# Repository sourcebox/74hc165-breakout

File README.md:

# About

KiCad project files of a breakout board containing 8 cascaded 74HC165
shift registers offering parallel-in/serial-out functionality.

This board is intended as microcontroller GPIO extension for prototyping purposes.

# License

CC-BY-4.0

By: Oliver Rockstedt <info@sourcebox.de>

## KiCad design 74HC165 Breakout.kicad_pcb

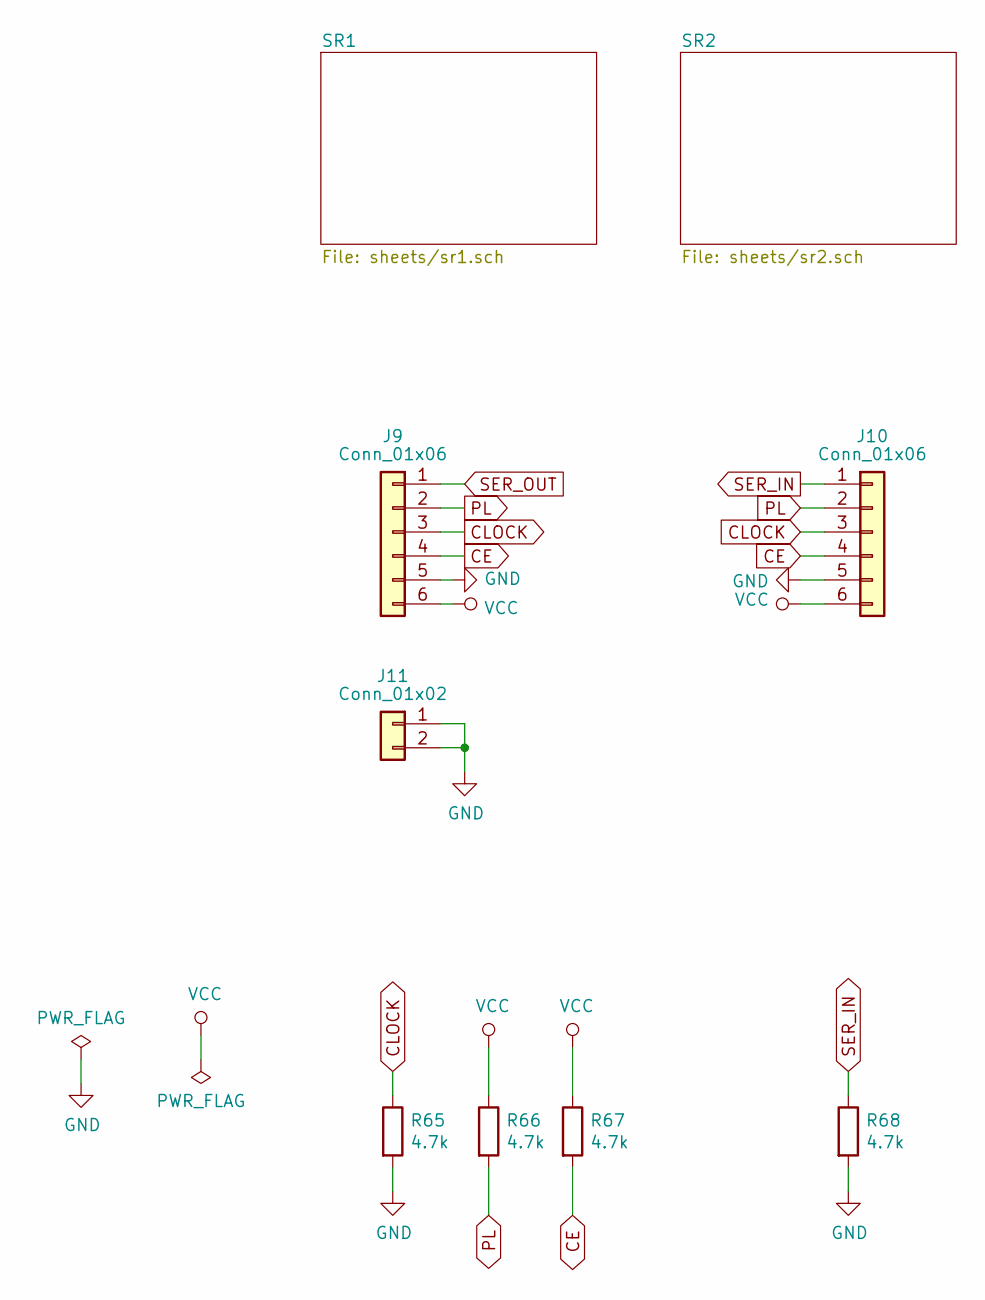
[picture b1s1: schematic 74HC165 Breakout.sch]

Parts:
J9, J10: Conn_01x06; PinHeader_1x06_P2.54mm_Vertical
J11: Conn_01x02; PinHeader_1x02_P2.54mm_Vertical
R65, R66, R67, R68: 4.7k; R_0805_2012Metric

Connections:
CE: J9.4, J10.4, R67.2; also elsewhere on the board
CLOCK: J9.3, J10.3, R65.1; also elsewhere on the board
GND: J9.5, J10.5, J11.1, J11.2, R65.2, R68.2; also elsewhere on the board
PL: J9.2, J10.2, R66.2; also elsewhere on the board
SER_IN: J10.1, R68.1; also elsewhere on the board
SER_OUT: J9.1; also elsewhere on the board
VCC: J9.6, J10.6, R66.1, R67.1; also elsewhere on the board

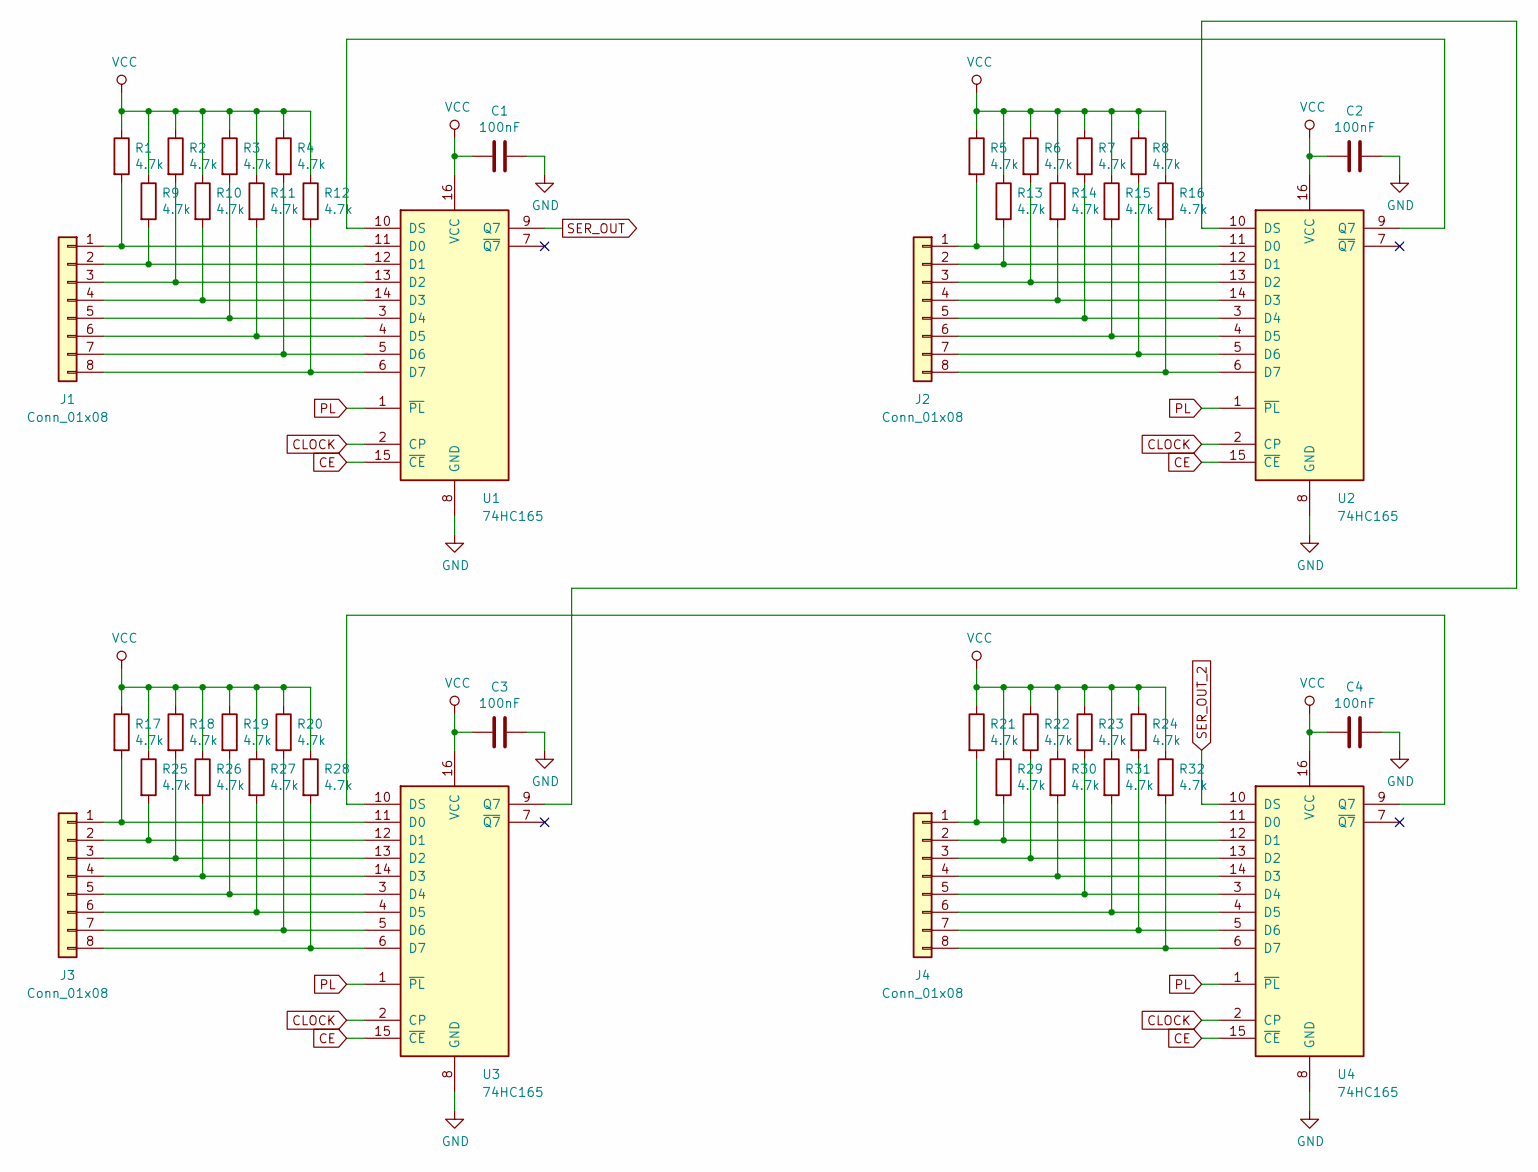
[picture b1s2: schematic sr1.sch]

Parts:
C1, C2, C3, C4: 100nF; C_0805_2012Metric
J1, J2, J3, J4: Conn_01x08; PinHeader_1x08_P2.54mm_Vertical
R1, R2, R3, R4, R5, R6, R7, R8, R9, R10, R11, R12, R13, R14, R15, R16, R17, R18, R19, R20, R21, R22, R23, R24, R25, R26, R27, R28, R29, R30, R31, R32: 4.7k; R_0805_2012Metric
U1, U2, U3, U4: 74HC165; SOIC-16_3.9x9.9mm_P1.27mm

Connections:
CE: U1.15 (~CE), U2.15 (~CE), U3.15 (~CE), U4.15 (~CE); also elsewhere on the board
CLOCK: U1.2 (CP), U2.2 (CP), U3.2 (CP), U4.2 (CP); also elsewhere on the board
GND: C1.1, C2.1, C3.1, C4.1, U1.8 (GND), U2.8 (GND), U3.8 (GND), U4.8 (GND); also elsewhere on the board
unnamed: J1.1, R1.2, U1.11 (D0)
unnamed: J1.2, R9.2, U1.12 (D1)
unnamed: J1.3, R2.2, U1.13 (D2)
unnamed: J1.4, R10.2, U1.14 (D3)
unnamed: J1.5, R3.2, U1.3 (D4)
unnamed: J1.6, R11.2, U1.4 (D5)
unnamed: J1.7, R4.2, U1.5 (D6)
unnamed: J1.8, R12.2, U1.6 (D7)
unnamed: J2.1, R5.2, U2.11 (D0)
unnamed: J2.2, R13.2, U2.12 (D1)
unnamed: J2.3, R6.2, U2.13 (D2)
unnamed: J2.4, R14.2, U2.14 (D3)
unnamed: J2.5, R7.2, U2.3 (D4)
unnamed: J2.6, R15.2, U2.4 (D5)
unnamed: J2.7, R8.2, U2.5 (D6)
unnamed: J2.8, R16.2, U2.6 (D7)
unnamed: J3.1, R17.2, U3.11 (D0)
unnamed: J3.2, R25.2, U3.12 (D1)
unnamed: J3.3, R18.2, U3.13 (D2)
unnamed: J3.4, R26.2, U3.14 (D3)
unnamed: J3.5, R19.2, U3.3 (D4)
unnamed: J3.6, R27.2, U3.4 (D5)
unnamed: J3.7, R20.2, U3.5 (D6)
unnamed: J3.8, R28.2, U3.6 (D7)
unnamed: J4.1, R21.2, U4.11 (D0)
unnamed: J4.2, R29.2, U4.12 (D1)
unnamed: J4.3, R22.2, U4.13 (D2)
unnamed: J4.4, R30.2, U4.14 (D3)
unnamed: J4.5, R23.2, U4.3 (D4)
unnamed: J4.6, R31.2, U4.4 (D5)
unnamed: J4.7, R24.2, U4.5 (D6)
unnamed: J4.8, R32.2, U4.6 (D7)
unnamed: U1.10 (DS), U2.9 (Q7)
unnamed: U2.10 (DS), U3.9 (Q7)
unnamed: U3.10 (DS), U4.9 (Q7)
PL: U1.1 (~PL), U2.1 (~PL), U3.1 (~PL), U4.1 (~PL); also elsewhere on the board
SER_OUT: U1.9 (Q7); also elsewhere on the board
SER_OUT_2: U4.10 (DS); also elsewhere on the board
VCC: C1.2, C2.2, C3.2, C4.2, R1.1, R2.1, R3.1, R4.1, R5.1, R6.1, R7.1, R8.1, R9.1, R10.1, R11.1, R12.1, R13.1, R14.1, R15.1, R16.1, R17.1, R18.1, R19.1, R20.1, R21.1, R22.1, R23.1, R24.1, R25.1, R26.1, R27.1, R28.1, R29.1, R30.1, R31.1, R32.1, U1.16 (VCC), U2.16 (VCC), U3.16 (VCC), U4.16 (VCC); also elsewhere on the board

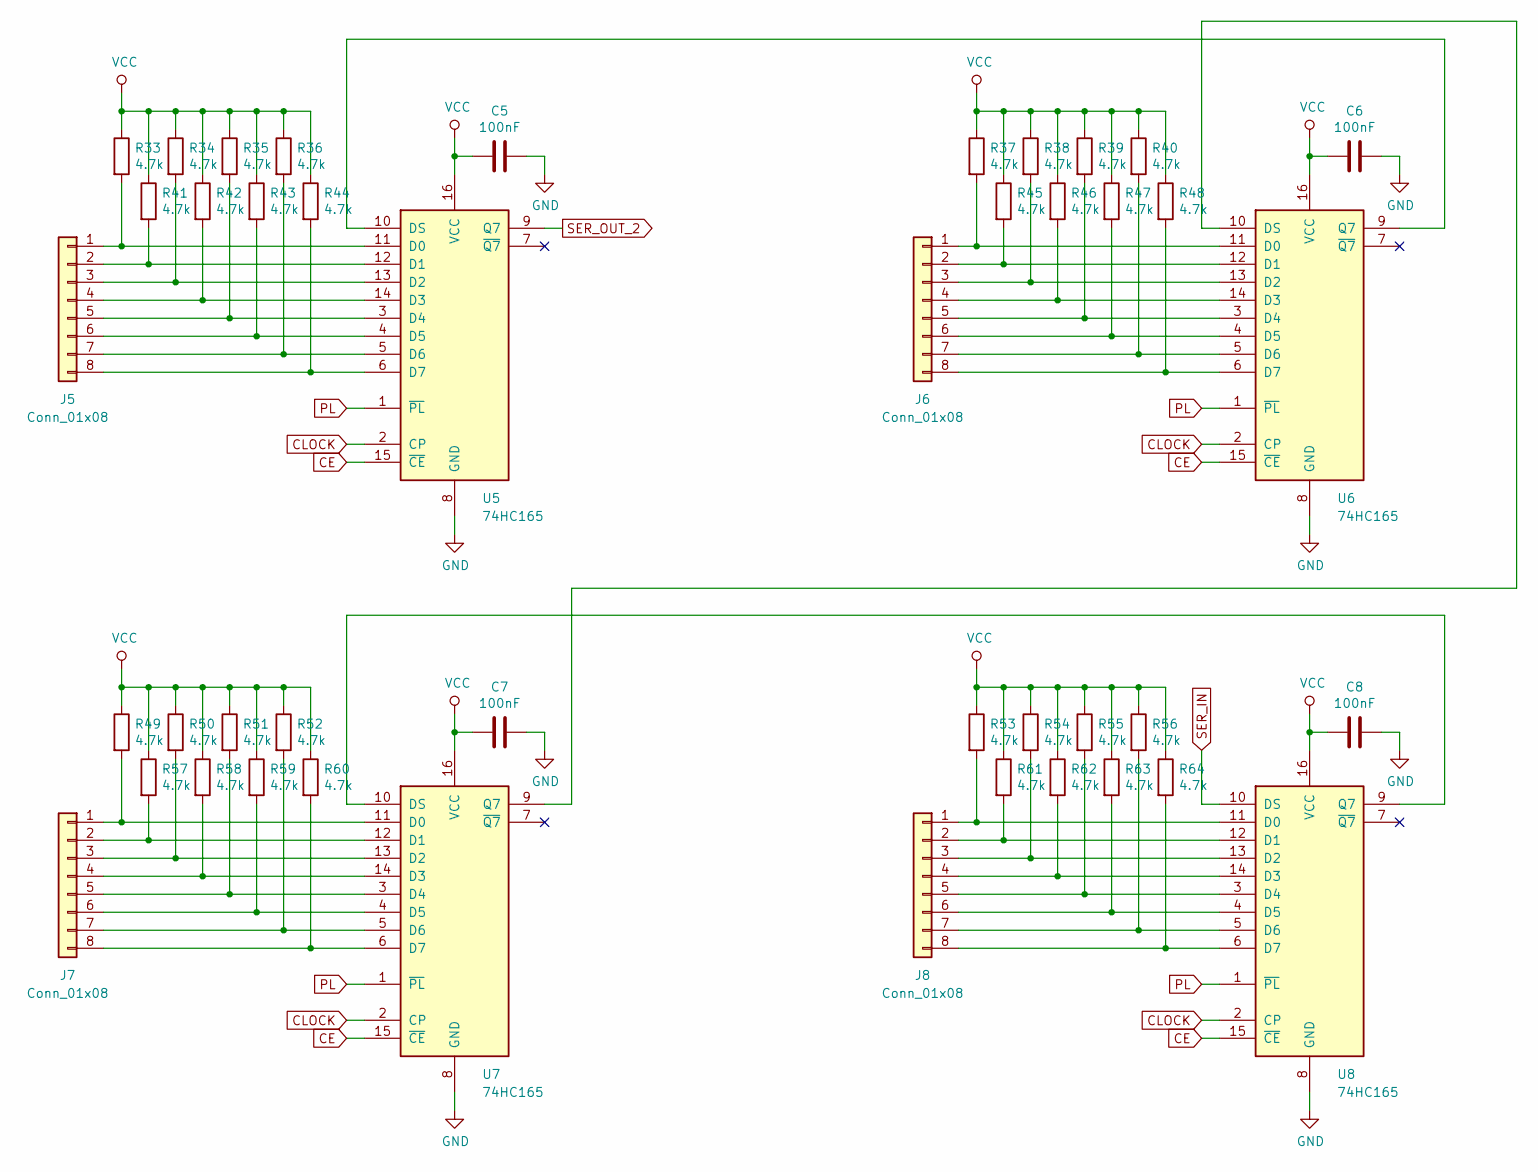
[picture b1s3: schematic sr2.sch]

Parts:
C5, C6, C7, C8: 100nF; C_0805_2012Metric
J5, J6, J7, J8: Conn_01x08; PinHeader_1x08_P2.54mm_Vertical
R33, R34, R35, R36, R37, R38, R39, R40, R41, R42, R43, R44, R45, R46, R47, R48, R49, R50, R51, R52, R53, R54, R55, R56, R57, R58, R59, R60, R61, R62, R63, R64: 4.7k; R_0805_2012Metric
U5, U6, U7, U8: 74HC165; SOIC-16_3.9x9.9mm_P1.27mm

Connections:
CE: U5.15 (~CE), U6.15 (~CE), U7.15 (~CE), U8.15 (~CE); also elsewhere on the board
CLOCK: U5.2 (CP), U6.2 (CP), U7.2 (CP), U8.2 (CP); also elsewhere on the board
GND: C5.1, C6.1, C7.1, C8.1, U5.8 (GND), U6.8 (GND), U7.8 (GND), U8.8 (GND); also elsewhere on the board
unnamed: J5.1, R33.2, U5.11 (D0)
unnamed: J5.2, R41.2, U5.12 (D1)
unnamed: J5.3, R34.2, U5.13 (D2)
unnamed: J5.4, R42.2, U5.14 (D3)
unnamed: J5.5, R35.2, U5.3 (D4)
unnamed: J5.6, R43.2, U5.4 (D5)
unnamed: J5.7, R36.2, U5.5 (D6)
unnamed: J5.8, R44.2, U5.6 (D7)
unnamed: J6.1, R37.2, U6.11 (D0)
unnamed: J6.2, R45.2, U6.12 (D1)
unnamed: J6.3, R38.2, U6.13 (D2)
unnamed: J6.4, R46.2, U6.14 (D3)
unnamed: J6.5, R39.2, U6.3 (D4)
unnamed: J6.6, R47.2, U6.4 (D5)
unnamed: J6.7, R40.2, U6.5 (D6)
unnamed: J6.8, R48.2, U6.6 (D7)
unnamed: J7.1, R49.2, U7.11 (D0)
unnamed: J7.2, R57.2, U7.12 (D1)
unnamed: J7.3, R50.2, U7.13 (D2)
unnamed: J7.4, R58.2, U7.14 (D3)
unnamed: J7.5, R51.2, U7.3 (D4)
unnamed: J7.6, R59.2, U7.4 (D5)
unnamed: J7.7, R52.2, U7.5 (D6)
unnamed: J7.8, R60.2, U7.6 (D7)
unnamed: J8.1, R53.2, U8.11 (D0)
unnamed: J8.2, R61.2, U8.12 (D1)
unnamed: J8.3, R54.2, U8.13 (D2)
unnamed: J8.4, R62.2, U8.14 (D3)
unnamed: J8.5, R55.2, U8.3 (D4)
unnamed: J8.6, R63.2, U8.4 (D5)
unnamed: J8.7, R56.2, U8.5 (D6)
unnamed: J8.8, R64.2, U8.6 (D7)
unnamed: U5.10 (DS), U6.9 (Q7)
unnamed: U6.10 (DS), U7.9 (Q7)
unnamed: U7.10 (DS), U8.9 (Q7)
PL: U5.1 (~PL), U6.1 (~PL), U7.1 (~PL), U8.1 (~PL); also elsewhere on the board
SER_IN: U8.10 (DS); also elsewhere on the board
SER_OUT_2: U5.9 (Q7); also elsewhere on the board
VCC: C5.2, C6.2, C7.2, C8.2, R33.1, R34.1, R35.1, R36.1, R37.1, R38.1, R39.1, R40.1, R41.1, R42.1, R43.1, R44.1, R45.1, R46.1, R47.1, R48.1, R49.1, R50.1, R51.1, R52.1, R53.1, R54.1, R55.1, R56.1, R57.1, R58.1, R59.1, R60.1, R61.1, R62.1, R63.1, R64.1, U5.16 (VCC), U6.16 (VCC), U7.16 (VCC), U8.16 (VCC); also elsewhere on the board

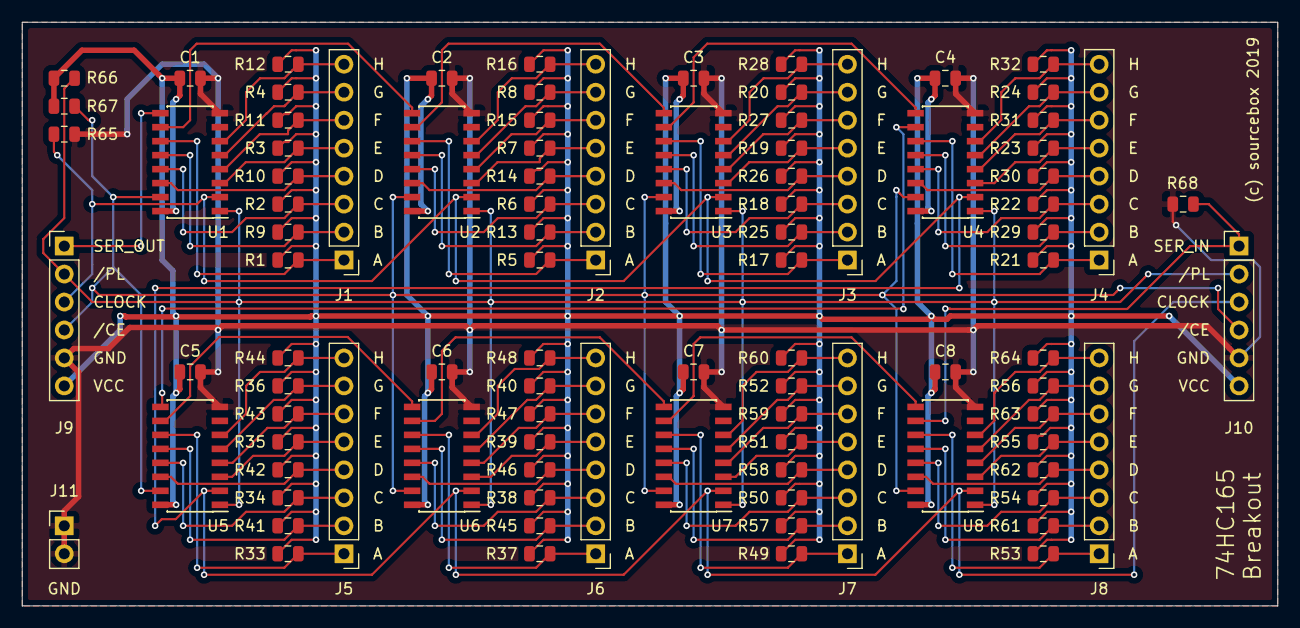
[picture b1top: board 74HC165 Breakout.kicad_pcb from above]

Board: 2 copper layers, 114.0 x 53.0 mm, 95 parts (0 on the bottom side), 78 nets.

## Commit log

2019-03-26 Schematics
2019-04-01 Routed
2019-04-09 Gerbers export
2021-03-04 License and readme
2021-12-26 PDF export
